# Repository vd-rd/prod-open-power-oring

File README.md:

# PowerPath controller with HotSwap protection

This module is designed to provide redundant power supply for power rails between 5-36V. Depending on the components that are populated on the board it can deliver up to 40A of current. The module can be used in a standalone configuration (switches are provided to select desired functionality) or can be controlled using the 2.54 pin header.

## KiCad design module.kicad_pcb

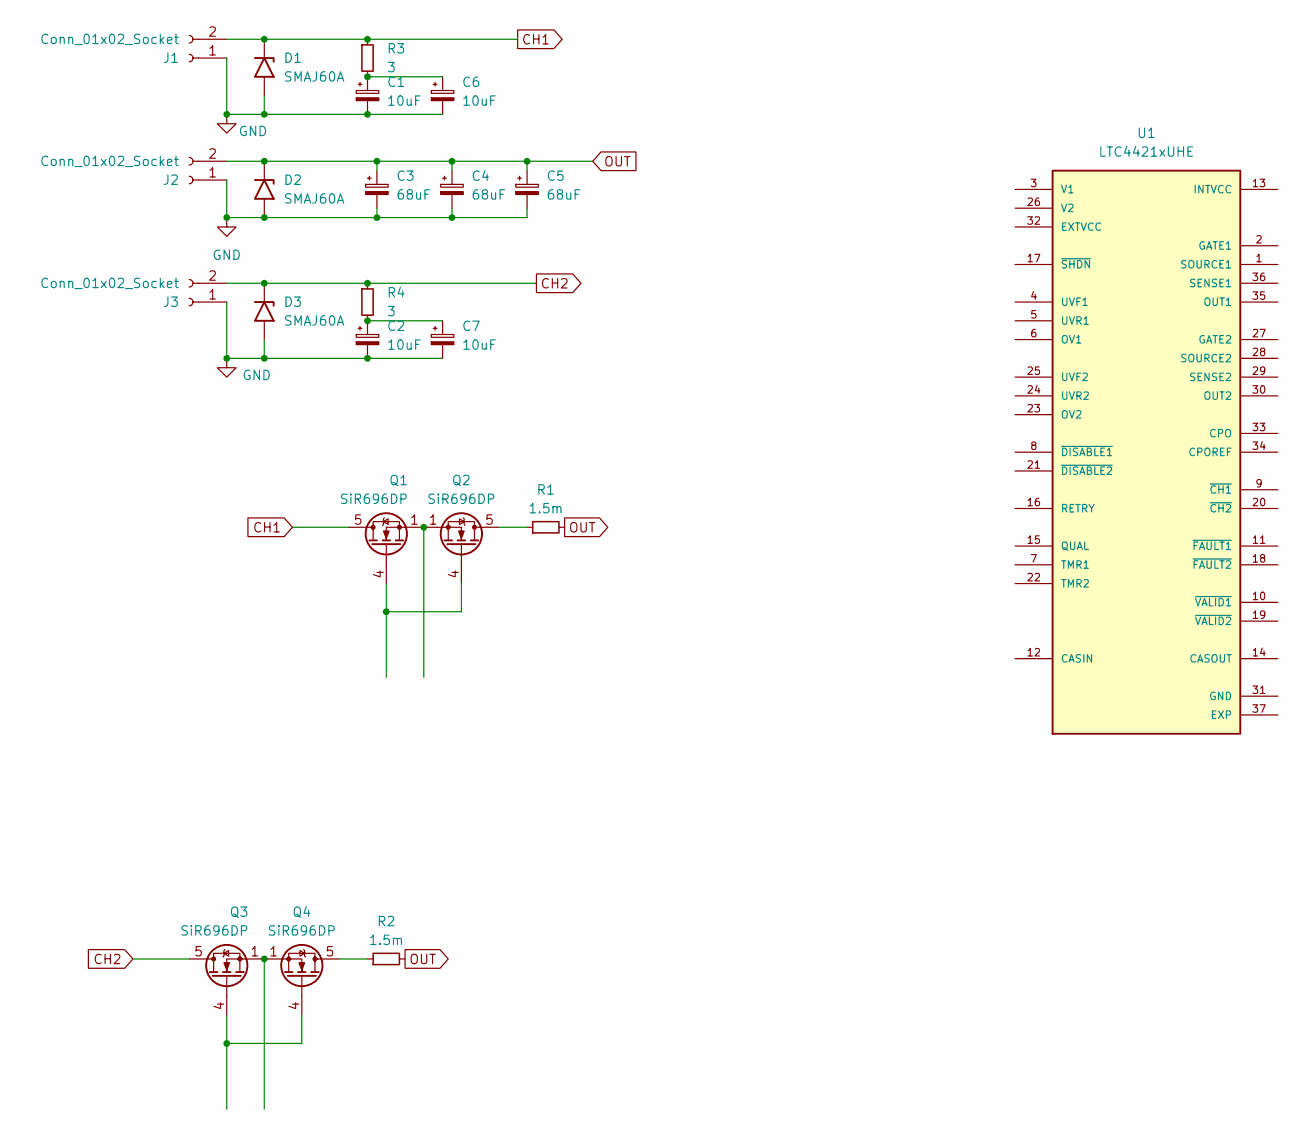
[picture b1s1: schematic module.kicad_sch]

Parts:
C1, C2, C6, C7: 10uF; CP_Elec_6.3x7.7; Voltage 100V
C3, C4, C5: 68uF; CP_Elec_10x10; Voltage 63V
D1, D2, D3: SMAJ60A; D_SMA
J1, J2, J3: Conn_01x02_Socket; AMASS_XT60PW-F_1x02_P7.20mm_Horizontal
Q1, Q2, Q3, Q4: SiR696DP; PowerPAK_SO-8_Single
R1, R2: 1.5m; R_2512_6332Metric
R3, R4: 3; R_1812_4532Metric
U1: LTC4421xUHE; QFN-36-1EP_5x6mm_P0.5mm_EP3.6x4.6mm_ThermalVias

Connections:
CH1: D1.1 (A1), J1.2, Q1.5 (D), R3.1
CH2: D3.1 (A1), J3.2, Q3.5 (D), R4.1
GND: C1.2, C2.2, C3.2, C4.2, C5.2, C6.2, C7.2, D1.2 (A2), D2.2 (A2), D3.2 (A2), J1.1, J2.1, J3.1
unnamed: C1.1, C6.1, R3.2
unnamed: C2.1, C7.1, R4.2
unnamed: Q1.4 (G), Q2.4 (G)
unnamed: Q1.1 (S), Q1.2 (S), Q1.3 (S), Q2.1 (S), Q2.2 (S), Q2.3 (S)
unnamed: Q2.5 (D), R1.1
unnamed: Q3.4 (G), Q4.4 (G)
unnamed: Q3.1 (S), Q3.2 (S), Q3.3 (S), Q4.1 (S), Q4.2 (S), Q4.3 (S)
unnamed: Q4.5 (D), R2.1
OUT: C3.1, C4.1, C5.1, D2.1 (A1), J2.2, R1.2, R2.2

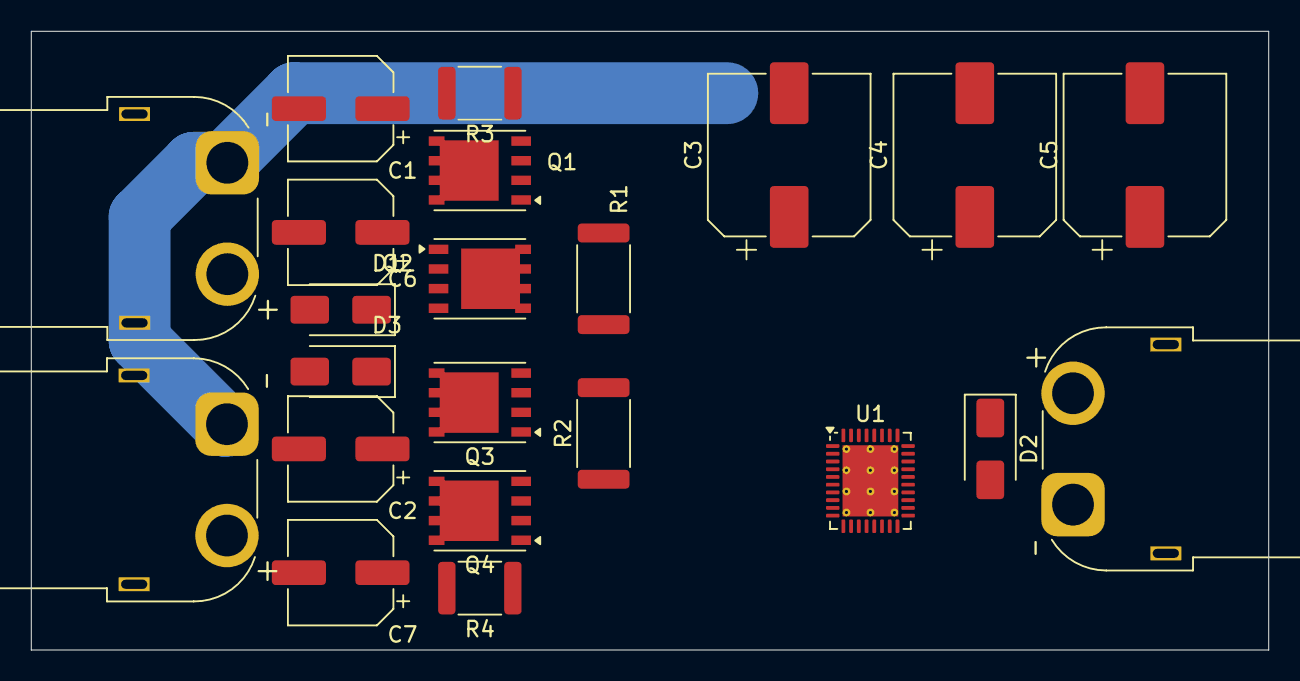
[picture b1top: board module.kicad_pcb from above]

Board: 2 copper layers, 80.0 x 40.0 mm, 22 parts (0 on the bottom side), 12 nets.

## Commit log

2020-11-21 project: initial floorplan
2020-11-21 project: define i/o
2020-11-22 project: add demoboard module
2020-11-23 project: finish features
2020-11-23 project: run drc and cosmetic fixes
2024-07-23 switched to kicad
2026-04-26 Refactor code structure for improved readability and maintainability
